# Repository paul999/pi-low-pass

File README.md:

pi-low-pass
===========

This is a basic PCB based on the work by @CurlyMoo (https://github.com/CurlyMoo/433.92-Raspberry-Pi) to control a 433.92mhz sender/receiver with your raspberry pi.

The PCB is based on the schema by CurlyMoo, and is released under the GPLv3.

Testing
===========
The PCB, as is in the repo, has currently not tested, and can contain mistakes. Iam currently waiting for a first batch of test PCBs to make sure everything is working fine.

PCB
===========
The PCB is created with Eagle, and uses primarly SMD components to reduce the size of the PCB. As far I can see, the source eagle files are XML. If you want to contribute a patch to these PCBs, please create a pull request for your changes.

Photos of the PCB
===========

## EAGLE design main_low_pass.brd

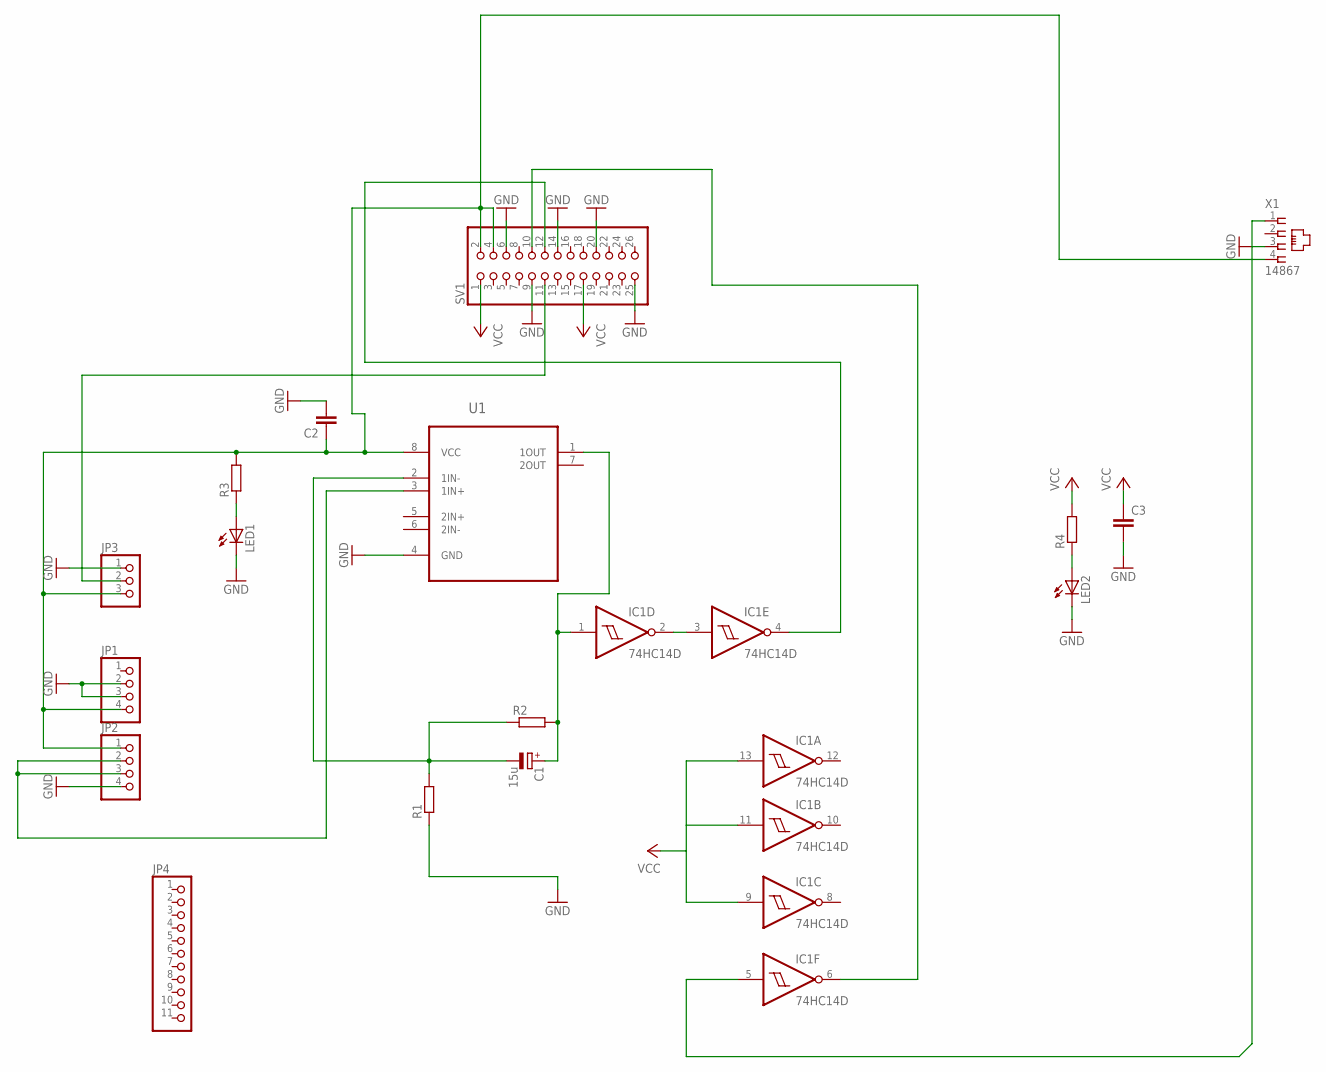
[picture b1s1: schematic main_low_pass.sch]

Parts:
C1: 15u; 153CLV-0605
C2, C3: C-EUC0805; C0805
IC1: 74HC14D; SO14
JP1, JP2: PINHD-1X4; 1X04
JP3: PINHD-1X3; 1X03
JP4: PINHD-1X11; 1X11
LED1, LED2: LEDCHIP-LED0805; CHIP-LED0805
R1, R2, R3, R4: R-EU_R0805; R0805
SV1: PINHD-2X13; 2X13
U1: LM358PW; SOP65P640X120-8N
X1: 14867

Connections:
GND: C2.2, C3.2, IC1.7 (GND), JP1.2, JP1.3, JP2.4, JP3.1, LED1.C, LED2.C, R1.1, SV1.6, SV1.9, SV1.14, SV1.20, SV1.25, U1.4 (GND), X1.3
unnamed: JP2.2, JP2.3, U1.3 (1IN+)
unnamed: C1.-, R1.2, R2.1, U1.2 (1IN-)
unnamed: IC1.2 (O), IC1.3 (I)
unnamed: IC1.5 (I), X1.1
unnamed: JP3.2, SV1.11
unnamed: C2.1, JP1.4, JP2.1, JP3.3, R3.2, SV1.2, SV1.4, U1.8 (VCC), X1.4
unnamed: C1.+, IC1.1 (I), R2.2, U1.1 (1OUT)
unnamed: LED1.A, R3.1
unnamed: LED2.A, R4.1
unnamed: IC1.4 (O), SV1.12
unnamed: IC1.6 (O), SV1.10
VCC: C3.1, IC1.9 (I), IC1.11 (I), IC1.13 (I), IC1.14 (VCC), R4.2, SV1.1, SV1.17

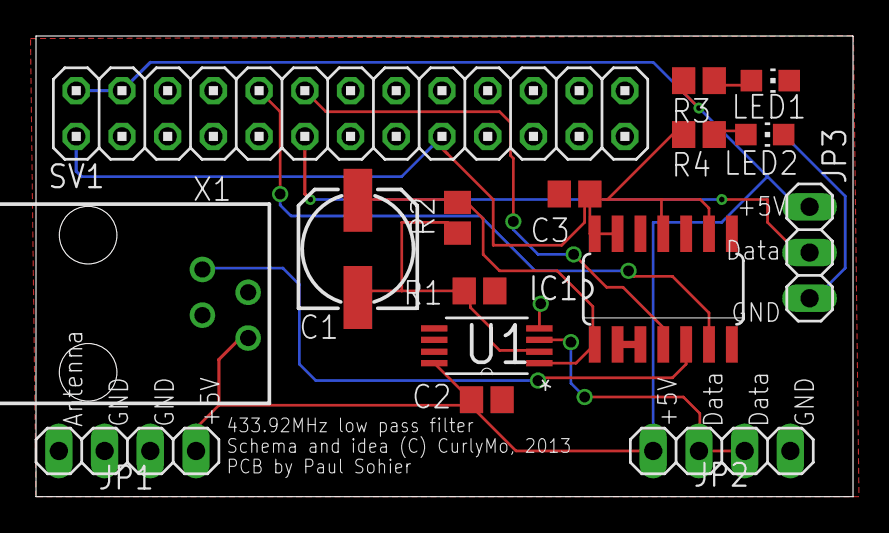
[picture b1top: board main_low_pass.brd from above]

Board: 2 copper layers, 45.4 x 25.6 mm, 16 parts (0 on the bottom side), 13 nets.

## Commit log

2013-08-03 First pass of the PCB. Please note this isnt finished and should not be used yet.
2013-08-03 Board update, alles moet nog nagemeten ed worden.
2013-08-03 Some updates to the PCB, and a first list of required components.
2013-08-03 SV1 verplaatst naar de zijkant ipv in het midden van het bord.
2013-08-03 replace input connector with a headerstrip so it can be clicked on a PI, and added a second strip that copies the input from the pie.
2013-08-03 Moved some stuff, tried adding a RJ1 connector as test.
2013-08-04 Nieuwste revisie, connector omgedraaid zodat hij op de PI kan, RJ11 toegevoegd voor slimme meter.
2013-08-29 Forgot a connection, removed outdated board files.
2013-08-29 Last few changes before submitting to production.
2013-09-06 Some first photos of the PCB. Iam still waiting for the IC and the ElCO, so it cant be finished yet.
2013-09-06 Lets see if this is the right URL...
2013-09-11 First set of fixes: Missed some connections to IC1
2013-09-15 Make sure the low pass filter actually fits the pi. this change causes the board to be outside the pi, but otherwise it hits the analog out.
